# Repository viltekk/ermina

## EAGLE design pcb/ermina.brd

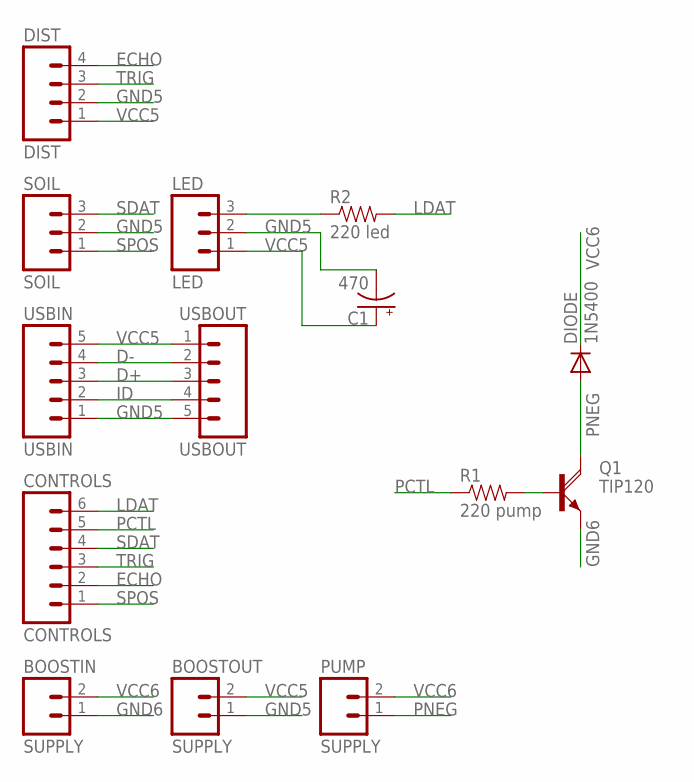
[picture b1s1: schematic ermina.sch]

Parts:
BOOSTIN: SUPPLY; 1X02_NO_SILK
BOOSTOUT: SUPPLY; 1X02_NO_SILK
C1: 470; CPOL-RADIAL-100UF-25V
CONTROLS: CONTROLS; 1X06_NO_SILK
DIODE: 1N5400; DO201-15
DIST: DIST; 1X04_NO_SILK
LED: LED; 1X03_NO_SILK
PUMP: SUPPLY; 1X02_NO_SILK
Q1: TIP120; TO220AV
R1: 220 pump; AXIAL-0.4
R2: 220 led; AXIAL-0.4
SOIL: SOIL; 1X03_NO_SILK
USBIN: USBIN; 1X05_NO_SILK
USBOUT: USBOUT; 1X05_NO_SILK

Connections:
D+: USBIN.3, USBOUT.3
D-: USBIN.4, USBOUT.2
ECHO: CONTROLS.2, DIST.4
GND5: BOOSTOUT.1, C1.2 (-), DIST.2, LED.2, SOIL.2, USBIN.1, USBOUT.5
GND6: BOOSTIN.1, Q1.E
ID: USBIN.2, USBOUT.4
LDAT: CONTROLS.6, R2.P$2 (2)
N0: Q1.B, R1.P$2 (2)
unnamed: LED.3, R2.P$1 (1)
PCTL: CONTROLS.5, R1.P$1 (1)
PNEG: DIODE.A, PUMP.1, Q1.C
SDAT: CONTROLS.4, SOIL.3
SPOS: CONTROLS.1, SOIL.1
TRIG: CONTROLS.3, DIST.3
VCC5: BOOSTOUT.2, C1.1 (+), DIST.1, LED.1, USBIN.5, USBOUT.1
VCC6: BOOSTIN.2, DIODE.C, PUMP.2

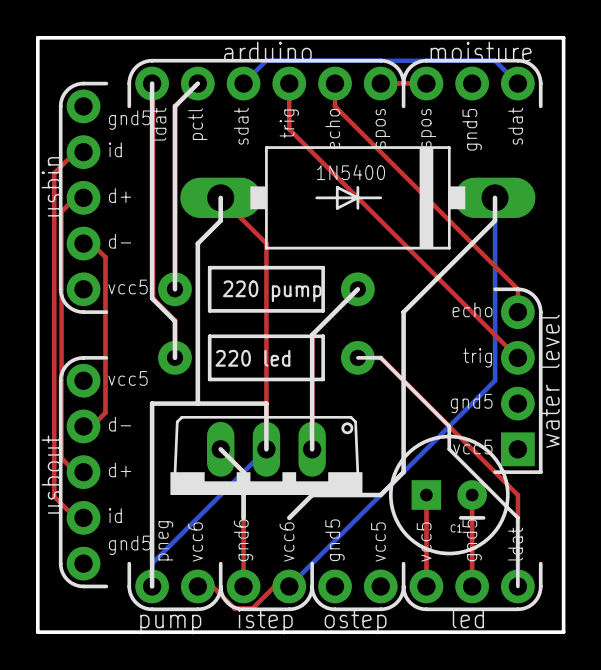
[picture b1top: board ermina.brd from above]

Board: 2 copper layers, 29.2 x 33.0 mm, 14 parts (0 on the bottom side), 16 nets.

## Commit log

2017-10-11 added cad files
2017-10-11 Device list and selection in place
2017-10-16 mainly some more work on the gauge view.
2017-10-25 worked on animations for moistureview
2017-10-30 added waterview
2017-10-31 status activity close to complete. need to polish icons and stuff
2017-11-01 under the good dev on viewstatusactivity
2017-11-02 graphical updates and started working on plant list
2017-11-07 changed xml format
2017-11-07 moved plants.xml to its own package and a lot of work done on SelectPlantActivity
2017-11-07 updated url to plants.xml
2017-11-07 added file for dummy plant generation and some ui tweaks
2017-11-07 error in plant generation
2017-11-07 plants.xml not updated at github?
2017-11-07 change plants.xml url
2017-11-07 some more tweaks..
2017-11-08 ui for custom plant is working. the ok button is not functional yet
2017-11-09 completed custom plant and changed animations in view status and custom plant
2018-05-08 cant remember why android stuff changed
2018-05-08 adding arduino stuff to repo
2018-05-08 shitload of cad stuff
2018-05-08 adding eagle stuff to repo
2018-05-08 bugfixes in bluetooth communication
2018-05-10 change interface in arduino code to match the one defined by android app
2018-05-20 updated plants db
2018-05-31 buttload of changes. commits like this should not be allowed..
2018-05-31 removed playground section in main loop
2018-05-31 removed unused defines
2018-06-11 modified data types
2018-06-11 modifications to cad and added leaves cad
2018-06-12 added more debug output
2018-07-09 more debug stuff
2018-09-12 removed integral part of pid controller and extended time between checks to 6 hours
2018-10-11 tried fixing millis rollover. might be causing problems with pump never activating

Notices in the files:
parts and their libraries:
SparkFun-Connectors: Licensing: Creative Commons ShareAlike 4.0 International - https://creativecommons.org/licenses/by-sa/4.0
